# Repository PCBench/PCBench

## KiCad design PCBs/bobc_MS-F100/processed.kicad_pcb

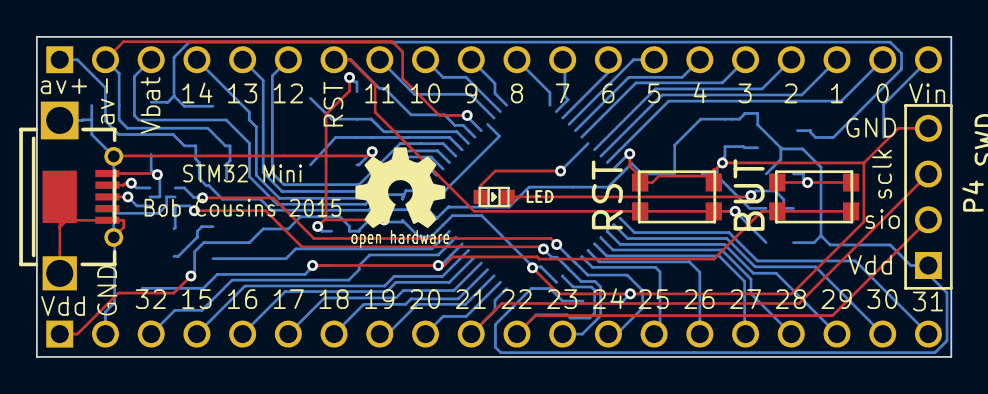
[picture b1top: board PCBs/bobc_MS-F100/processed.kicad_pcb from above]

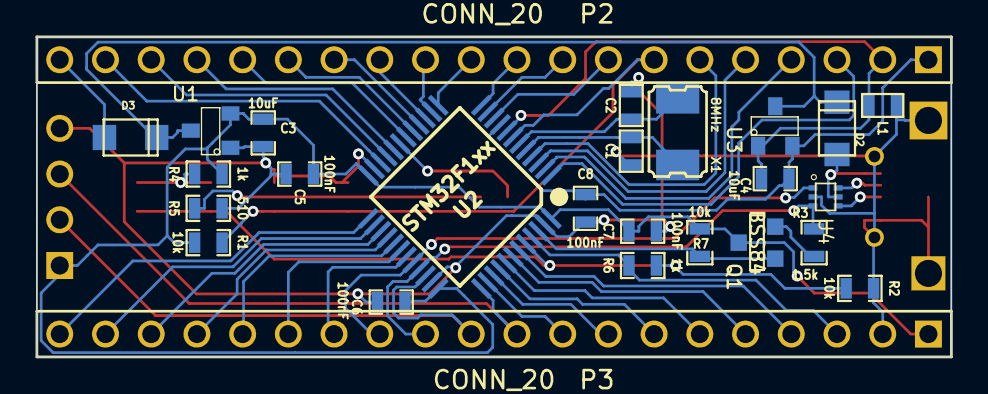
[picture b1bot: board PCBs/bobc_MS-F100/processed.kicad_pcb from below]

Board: 2 copper layers, 50.8 x 17.8 mm, 33 parts (26 on the bottom side), 52 nets.

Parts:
C1, C2: 20pF; SM0603_Capa
C3, C4: 10uF; SM0603_Capa
C5, C6, C7, C8: 100nF; SM0603_Capa
D1: LED; Led_0603
D2, D3: DIOD; do219ab
L1: IND; SM0603
M1: LOGO_OSHW; Logo_silk_OSHW_6x6mm
M2: PCB_GREEN_RMC; PCB_GREEN
P1: USBCONN; USB_MICRO_RMC
P2, P3: CONN_20; pin_header_2.54mm_1x20
P4: SWD; pin_header_2.54mm_1x4
Q1: BSS84; SOT23GDS
R1, R2, R7: 10k; SM0603_Resistor
R3: 1.5k; SM0603_Resistor
R4, R6: 1k; SM0603_Resistor
R5: 510; SM0603_Resistor
SW1: RST; SW_C&K_KMR4
SW2: BUT; SW_C&K_KMR4
U1, U3: MCP1703_SOT23; SOT23
U2: STM32F1xx; QFP48_0.5mm_7x7mm_SOT313_LPC1343
U4: NUF2042; SOT-563
X1: 8MHz; crystal_smd_5x3.2mm

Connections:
/AV+: C4.1, C8.1, P2.1, U2.9, U3.2
/AV-: C4.2, L1.2, P2.2, U2.8, U3.1
/BOOT0: R2.1, R6.2, SW2.1, U2.44
/D0: P2.19, U2.22
/D1: P2.18, U2.21
/D2: P2.17, U2.20
/D3: P2.16, U2.18
/D4: P2.15, U2.17
/D5: P2.14, U2.16
/D6: P2.13, U2.15
/D7: P2.12, U2.14
/D8: P2.11, U2.13
/D9: P2.10, U2.12
/D10: P2.9, U2.11
/D11: P2.8, U2.10
/D12: P2.6, U2.4
/D13: P2.5, U2.3
/D14: P2.4, U2.2
/D15: P3.4, U2.43
/D16: P3.5, U2.42
/D17: P3.6, U2.41
/D18: P3.7, U2.40
/D19: P3.8, U2.39
/D20: P3.9, U2.38
/D21_SWCLK: P3.10, P4.3, U2.37
/D22_SWIO: P3.11, P4.2, U2.34
/D23_USBDP: P3.12, R3.2, U2.33, U4.3
/D24_USBDM: P3.13, U2.32, U4.1
/D25: P3.14, U2.31
/D26: P3.15, U2.30
/D27: P3.16, U2.29
/D28: P3.17, U2.28
/D29: P3.18, U2.27
/D30: P3.19, U2.26
/D31: P3.20, U2.25
/D32: P3.3, R6.1, U2.45
/D33: D1.1, U2.19
/DISC: Q1.G, R7.2, U2.46
/VBAT: P2.3, U2.1
/VBUS: D2.1, P1.1, U4.5
/nRESET: P2.7, R1.2, SW1.2, U2.7
GND: C1.2, C2.2, C3.2, C5.2, C6.2, C7.2, C8.2, L1.1, P1.4, P1.5, P3.2, P4.4, R2.2, R5.2, SW1.1, U1.1, U2.23, U2.35, U2.47, U4.2
unnamed: R4.2, SW2.2
unnamed: D1.2, R5.1
unnamed: Q1.S, R3.1
unnamed: C1.1, U2.5, X1.1
unnamed: C2.1, U2.6, X1.2
unnamed: P1.3, U4.4
unnamed: D2.2, D3.2, U1.3, U3.3
unnamed: P1.2, U4.6
VDD: C3.1, C5.1, C6.1, C7.1, P3.1, P4.1, Q1.D, R1.1, R4.1, R7.1, U1.2, U2.24, U2.36, U2.48
VIN: D3.1, P2.20

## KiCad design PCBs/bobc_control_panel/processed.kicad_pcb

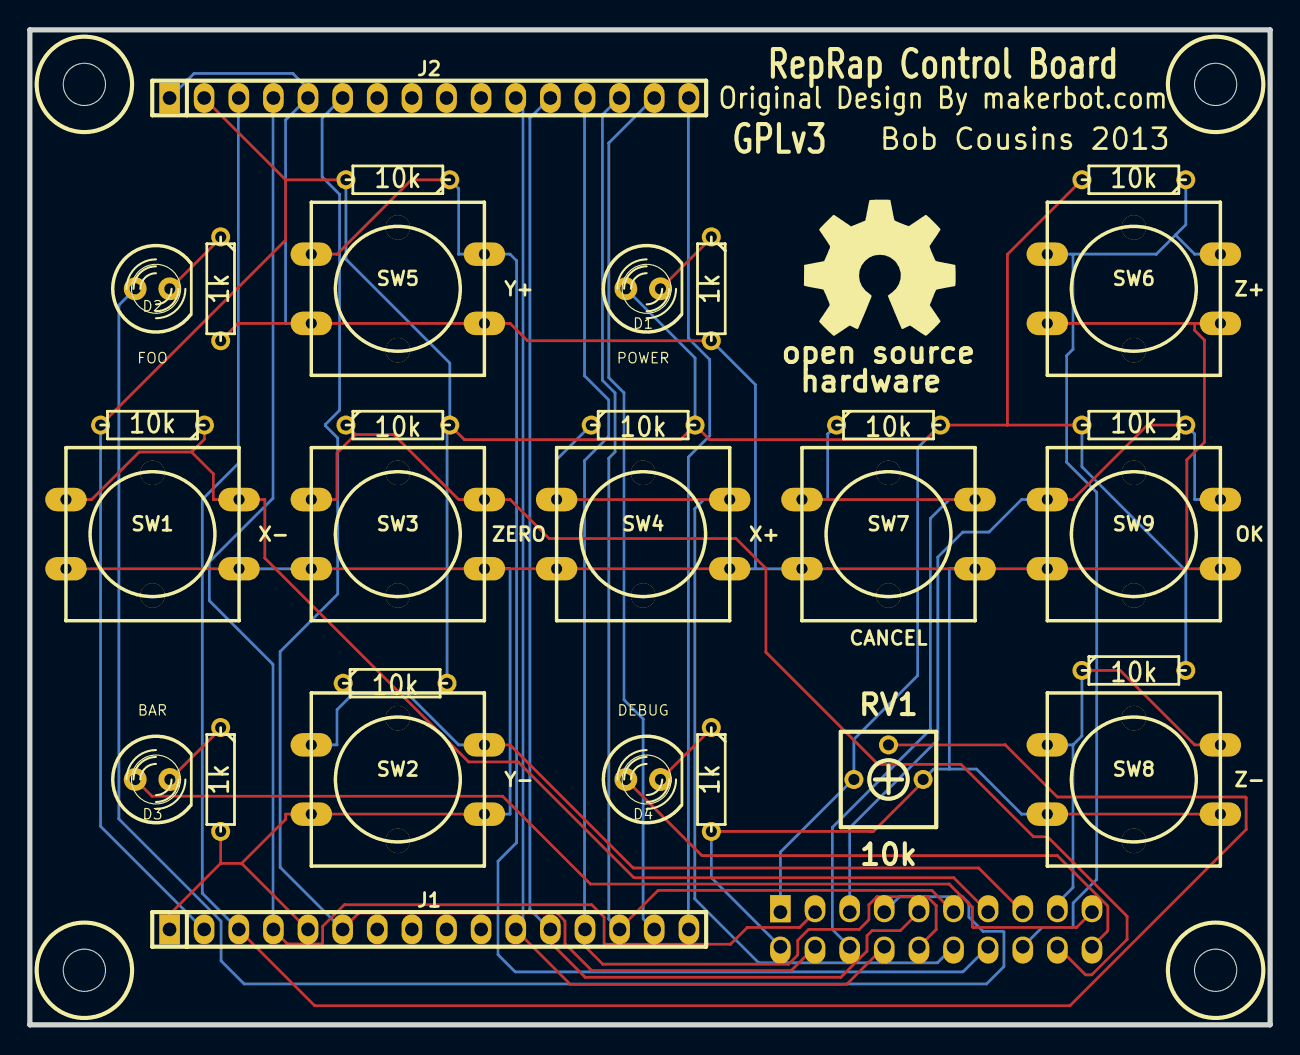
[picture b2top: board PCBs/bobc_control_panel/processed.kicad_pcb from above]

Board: 2 copper layers, 91.0 x 73.0 mm, 35 parts (1 on the bottom side), 27 nets.

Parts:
D1: POWER; LED-5MM
D2: FOO; LED-5MM
D3: BAR; LED-5MM
D4: DEBUG; LED-5MM
G1: LOGO; OSHW_logo_2
HOLE_M31, HOLE_M32, HOLE_M33, HOLE_M34: P***; HOLE_M3
J1, J2: LCD; pin_strip_16
P1: CONN_10X2; vasch_strip_10x2
R1, R2, R3, R4, R5, R7, R9, R11, R13: 10k; R3
R6, R8, R10, R12: 1k; R3
RV1: 10k; TRIM-BOURNS-3362
SW1: X-; SW_PUSH-12mm_RMC
SW2: Y-; SW_PUSH-12mm_RMC
SW3: ZERO; SW_PUSH-12mm_RMC
SW4: X+; SW_PUSH-12mm_RMC
SW5: Y+; SW_PUSH-12mm_RMC
SW6: Z+; SW_PUSH-12mm_RMC
SW7: CANCEL; SW_PUSH-12mm_RMC
SW8: Z-; SW_PUSH-12mm_RMC
SW9: OK; SW_PUSH-12mm_RMC

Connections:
/B_CANCEL: P1.6, R9.1, SW7.1
/B_OK: P1.5, R13.1, SW9.1
/B_X+: P1.12, R4.1, SW4.1
/B_X-: P1.13, R1.1, SW1.1
/B_Y+: P1.14, R5.1, SW5.1
/B_Y-: P1.15, R2.1, SW2.1
/B_Z+: P1.16, R7.1, SW6.1
/B_Z-: P1.17, R11.1, SW8.1
/B_ZERO: P1.18, R3.1, SW3.1
/LCD_BACKLIGHT+: J1.15, J2.15
/LCD_BACKLIGHT-: J1.16, J2.16
/LCD_CONTRAST: J1.3, J2.3, RV1.2
/LCD_D4: J1.11, J2.11, P1.8
/LCD_D5: J1.12, J2.12, P1.9
/LCD_D6: J1.13, J2.13, P1.10
/LCD_D7: J1.14, J2.14, P1.11
/LCD_ENABLE: J1.6, J2.6, P1.4
/LCD_RS: J1.4, J2.4, P1.3
/LED1: D2.1, P1.7
/LED2: D3.1, P1.19
/LED3: D4.1, P1.20
GND: J1.1, J1.5, J2.1, J2.5, P1.2, R6.2, R8.2, R10.2, R12.2, RV1.3, SW1.2, SW2.2, SW3.2, SW4.2, SW5.2, SW6.2, SW7.2, SW8.2, SW9.2
unnamed: D2.2, R8.1
unnamed: D1.2, R6.1
unnamed: D4.2, R12.1
unnamed: D3.2, R10.1
VCC: D1.1, J1.2, J2.2, P1.1, R1.2, R2.2, R3.2, R4.2, R5.2, R7.2, R9.2, R11.2, R13.2, RV1.1

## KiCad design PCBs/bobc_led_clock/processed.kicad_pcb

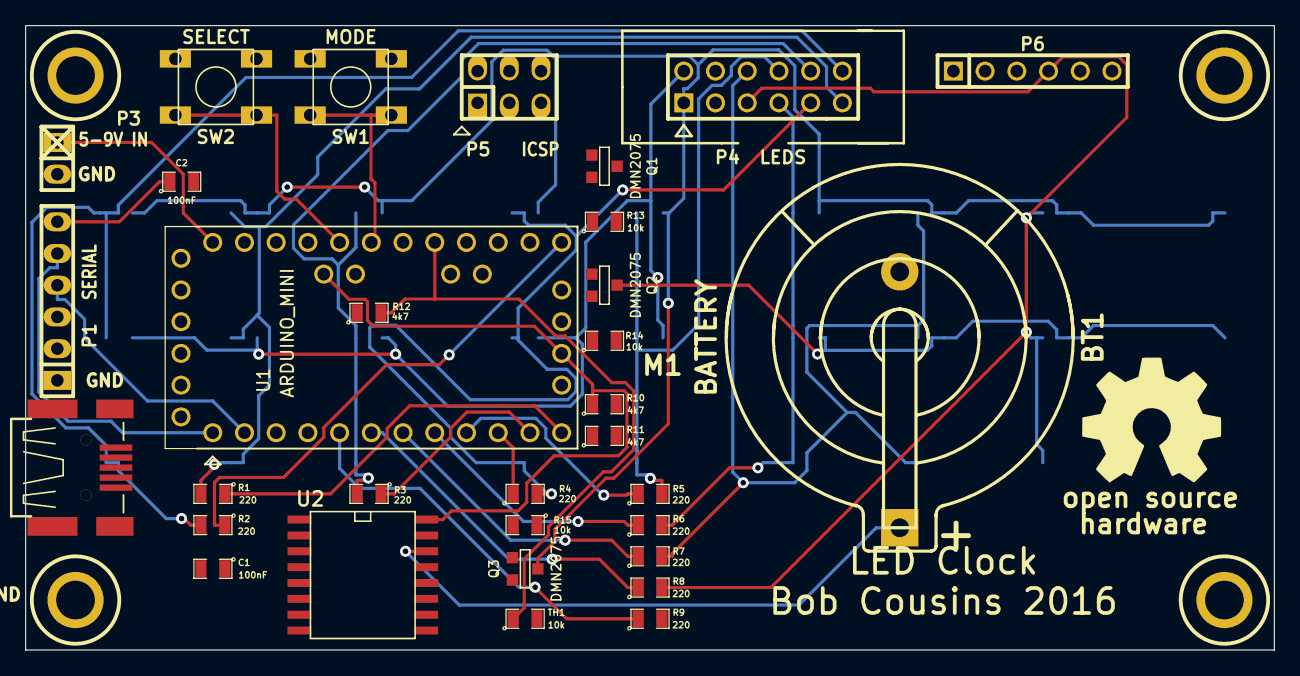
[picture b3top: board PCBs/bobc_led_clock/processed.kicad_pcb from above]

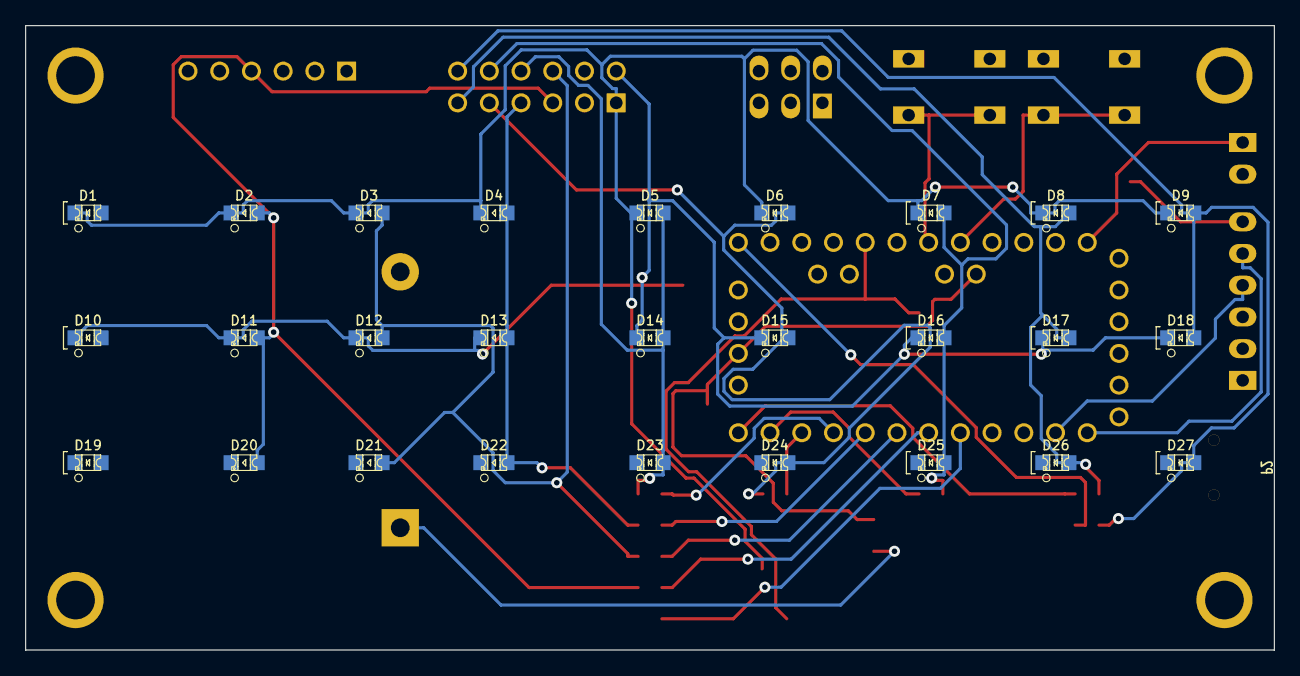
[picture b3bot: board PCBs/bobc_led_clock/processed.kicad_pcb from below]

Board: 2 copper layers, 100.0 x 50.0 mm, 65 parts (27 on the bottom side), 28 nets.

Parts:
BT1: BATTERY; keystone_106
C1, C2: 100nF; SM0805
D1, D7, D8, D9, D10, D16, D17, D18, D19, D25, D26, D27: LED; LED-0805_RED
D2, D3, D4, D11, D12, D13, D20, D21, D22: LED; LED-0805_GREEN
D5, D6, D14, D15, D23, D24: LED; LED-0805_BLUE
H1, H2, H3, H4: HOLE_RMC; HOLE_M3
M1: PCB_GREEN_RMC
M2: LOGO_OSHW; OSHW_logo_2
P1: SERIAL; pin_strip_6
P2: CONN_5; CONN_MiniAB_SMT_RMC
P3: 5-9V IN; pin_strip_2
P4: LEDS; PIN_ARRAY_6x2_RMC
P5: ICSP; pin_strip_3x2
P6: CONN_6; PIN_ARRAY-6X1
Q1, Q2, Q3: DMN2075; SOT23GDS
R1, R2, R3, R4, R5, R6, R7, R8, R9: 220; SM0805
R10, R11, R12: 4k7; SM0805
R13, R14, R15: 10k; SM0805
SW1: MODE; SW_6x6_MULTI
SW2: SELECT; SW_6x6_MULTI
TH1: 10k; SM0805
U1: ARDUINO_MINI
U2: DS3231N; SO16L

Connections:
/SCL: R10.1, U1.A5, U2.16
/SW1: SW1.1, U1.A2
/SW2: SW2.1, U1.A3
/VIN: P3.1, U1.VIN
COL2: D2.1, D11.1, D20.1, P4.5, P6.4, R8.2
COL3: D3.1, D12.1, D21.1, P4.6, R7.2
COL4: D4.1, D13.1, D22.1, P4.7, R6.2
COL5: D5.1, D14.1, D23.1, P4.8, R5.2
COL6: D6.1, D15.1, D24.1, P4.9, R4.2
COL7: D7.1, D16.1, D25.1, P4.10, R3.2
COL8: D8.1, D17.1, D26.1, P4.11, R2.2
COL9: D9.1, D18.1, D27.1, P4.12, R1.2
unnamed: R5.1, U1.6
unnamed: R6.1, U1.5
unnamed: R7.1, U1.4
unnamed: R8.1, U1.3
unnamed: R9.1, U1.2
unnamed: R4.1, U1.7
unnamed: C2.1, P1.6
unnamed: R1.1, U1.10
unnamed: R2.1, U1.9
unnamed: R3.1, U1.8
unnamed: R12.2, TH1.1, U1.A0
unnamed: BT1.1, U2.14
ROW1: D1.2, D2.2, D3.2, D4.2, D5.2, D6.2, D7.2, D8.2, D9.2, P4.1, Q3.D
ROW2: D10.2, D11.2, D12.2, D13.2, D14.2, D15.2, D16.2, D17.2, D18.2, P4.2, Q2.D
RX: P1.4, U1.0
TX: P1.5, U1.1

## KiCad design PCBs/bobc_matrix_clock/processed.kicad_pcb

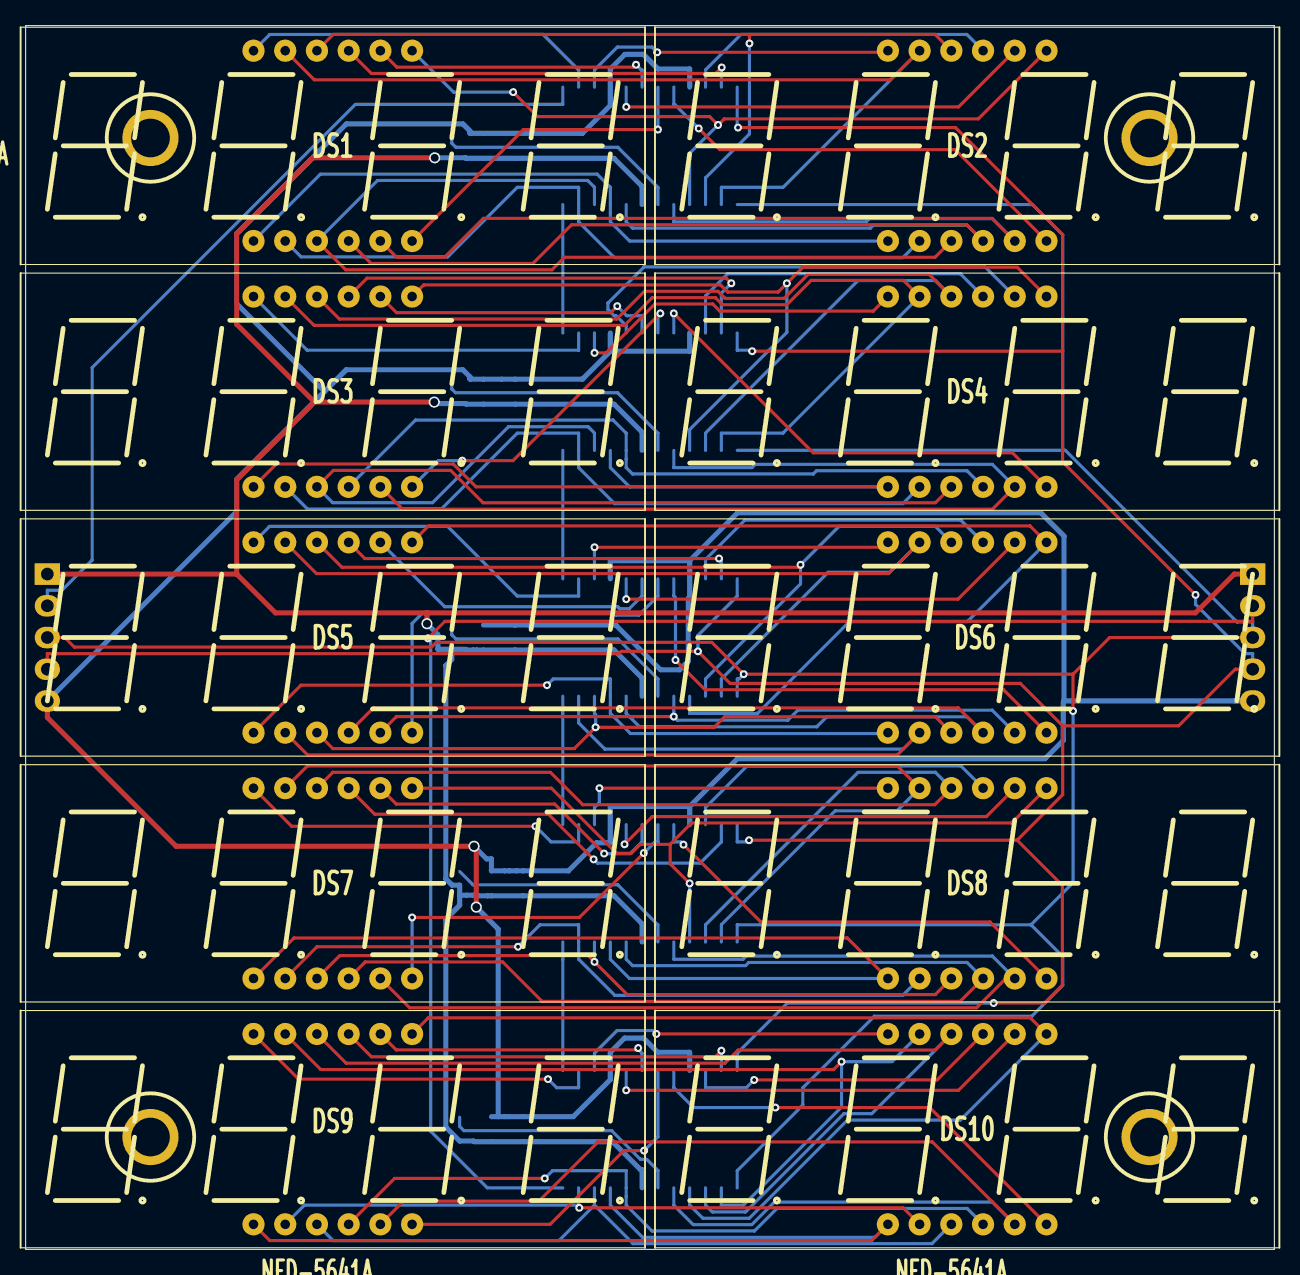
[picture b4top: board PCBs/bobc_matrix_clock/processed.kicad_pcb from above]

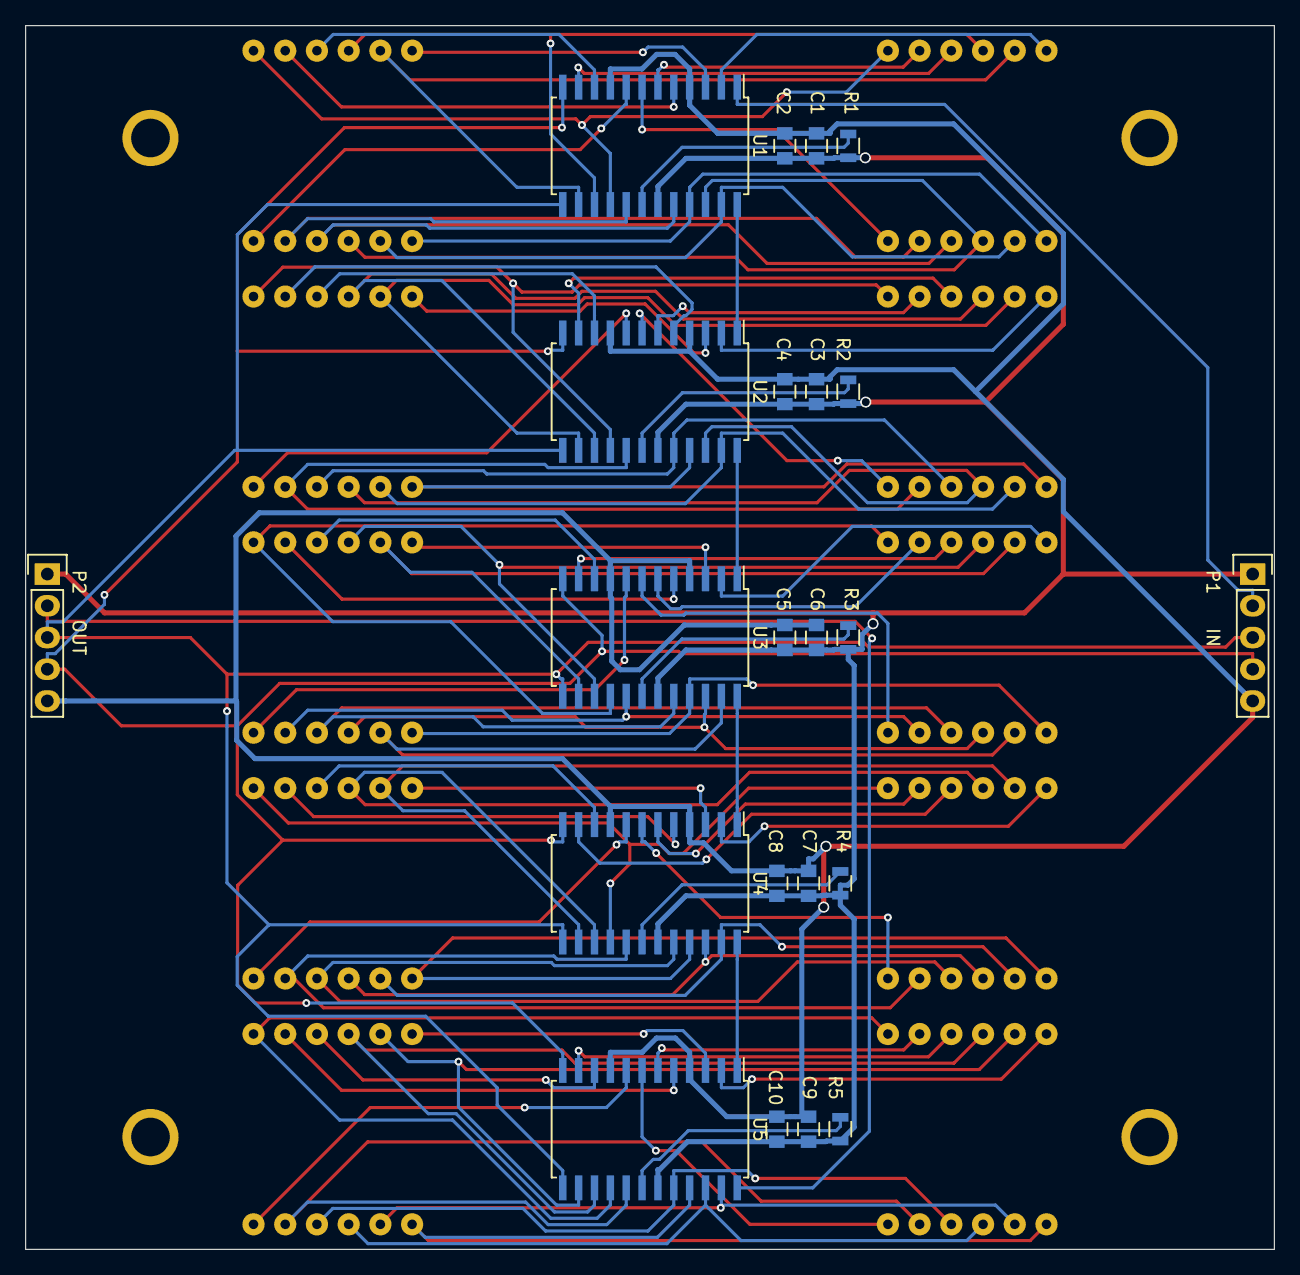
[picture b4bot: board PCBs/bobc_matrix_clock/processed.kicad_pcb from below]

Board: 2 copper layers, 100.0 x 98.0 mm, 36 parts (22 on the bottom side), 95 nets.

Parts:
C1, C3, C5, C7, C9: 10uF; C_0805
C2, C4, C6, C8, C10: 100nF; C_0805
DS1, DS2, DS3, DS4, DS5, DS6, DS7, DS8, DS9, DS10: NFD-5641A; NFD-5641
H1, H2, H3, H4: HOLE_RMC; HOLE_M3
P1: IN; Socket_Strip_Straight_1x05
P2: OUT; Socket_Strip_Straight_1x05
R1, R2, R3, R4, R5: 28k; R_0805
U1, U2, U3, U4, U5: MAX7219; SOIC-24_7.5x15.4mm_Pitch1.27mm

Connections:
/Digits Row 1/CLK: P1.3, P2.3, U1.13, U2.13, U3.13, U4.13, U5.13
/Digits Row 1/DIN: P1.2, U1.1
/Digits Row 1/LOAD: P1.4, P2.4, U1.12, U2.12, U3.12, U4.12, U5.12
/Digits Row 1/SEG_A: DS1.11, DS2.11, U1.14
/Digits Row 1/SEG_B: DS1.7, DS2.7, U1.16
/Digits Row 1/SEG_C: DS1.4, DS2.4, U1.20
/Digits Row 1/SEG_D: DS1.2, DS2.2, U1.23
/Digits Row 1/SEG_DP: DS1.3, DS2.3, U1.22
/Digits Row 1/SEG_E: DS1.1, DS2.1, U1.21
/Digits Row 1/SEG_F: DS1.10, DS2.10, U1.15
/Digits Row 1/SEG_G: DS1.5, DS2.5, U1.17
/Row 2/DIN: U1.24, U2.1
/Row 2/SEG_A: DS3.11, DS4.11, U2.14
/Row 2/SEG_B: DS3.7, DS4.7, U2.16
/Row 2/SEG_C: DS3.4, DS4.4, U2.20
/Row 2/SEG_D: DS3.2, DS4.2, U2.23
/Row 2/SEG_DP: DS3.3, DS4.3, U2.22
/Row 2/SEG_E: DS3.1, DS4.1, U2.21
/Row 2/SEG_F: DS3.10, DS4.10, U2.15
/Row 2/SEG_G: DS3.5, DS4.5, U2.17
/Row 3/DIN: U2.24, U3.1
/Row 3/SEG_A: DS5.11, DS6.11, U3.14
/Row 3/SEG_B: DS5.7, DS6.7, U3.16
/Row 3/SEG_C: DS5.4, DS6.4, U3.20
/Row 3/SEG_D: DS5.2, DS6.2, U3.23
/Row 3/SEG_DP: DS5.3, DS6.3, U3.22
/Row 3/SEG_E: DS5.1, DS6.1, U3.21
/Row 3/SEG_F: DS5.10, DS6.10, U3.15
/Row 3/SEG_G: DS5.5, DS6.5, U3.17
/Row 4/DIN: U3.24, U4.1
/Row 4/SEG_A: DS7.11, DS8.11, U4.14
/Row 4/SEG_B: DS7.7, DS8.7, U4.16
/Row 4/SEG_C: DS7.4, DS8.4, U4.20
/Row 4/SEG_D: DS7.2, DS8.2, U4.23
/Row 4/SEG_DP: DS7.3, DS8.3, U4.22
/Row 4/SEG_E: DS7.1, DS8.1, U4.21
/Row 4/SEG_F: DS7.10, DS8.10, U4.15
/Row 4/SEG_G: DS7.5, DS8.5, U4.17
/Row 5/DIN: U4.24, U5.1
/Row 5/DOUT: P2.2, U5.24
/Row 5/SEG_A: DS9.11, DS10.11, U5.14
/Row 5/SEG_B: DS9.7, DS10.7, U5.16
/Row 5/SEG_C: DS9.4, DS10.4, U5.20
/Row 5/SEG_D: DS9.2, DS10.2, U5.23
/Row 5/SEG_DP: DS9.3, DS10.3, U5.22
/Row 5/SEG_E: DS9.1, DS10.1, U5.21
/Row 5/SEG_F: DS9.10, DS10.10, U5.15
/Row 5/SEG_G: DS9.5, DS10.5, U5.17
GND: C1.2, C2.2, C3.2, C4.2, C5.2, C6.2, C7.2, C8.2, C9.2, C10.2, P1.5, P2.5, U1.4, U1.9, U2.4, U2.9, U3.4, U3.9, U4.4, U4.9, U5.4, U5.9
unnamed: DS1.6, U1.7
unnamed: DS1.8, U1.6
unnamed: DS1.9, U1.11
unnamed: DS1.12, U1.2
unnamed: DS2.6, U1.8
unnamed: DS2.8, U1.5
unnamed: DS2.9, U1.10
unnamed: DS2.12, U1.3
unnamed: DS3.6, U2.7
unnamed: DS3.8, U2.6
unnamed: DS3.9, U2.11
unnamed: DS3.12, U2.2
unnamed: DS4.6, U2.8
unnamed: DS4.8, U2.5
unnamed: DS4.9, U2.10
unnamed: DS4.12, U2.3
unnamed: DS5.6, U3.7
unnamed: DS5.8, U3.6
unnamed: DS5.9, U3.11
unnamed: DS5.12, U3.2
unnamed: DS6.6, U3.8
unnamed: DS6.8, U3.5
unnamed: DS6.9, U3.10
unnamed: DS6.12, U3.3
unnamed: DS7.6, U4.7
unnamed: DS7.8, U4.6
unnamed: DS7.9, U4.11
unnamed: DS7.12, U4.2
unnamed: DS8.6, U4.8
unnamed: DS8.8, U4.5
unnamed: DS8.9, U4.10
unnamed: DS8.12, U4.3
unnamed: DS9.6, U5.7
unnamed: DS9.8, U5.6
unnamed: DS9.9, U5.11
unnamed: DS9.12, U5.2
unnamed: DS10.6, U5.8
unnamed: DS10.8, U5.5
unnamed: DS10.9, U5.10
unnamed: DS10.12, U5.3
unnamed: R1.2, U1.18
unnamed: R2.2, U2.18
unnamed: R3.2, U3.18
unnamed: R4.2, U4.18
unnamed: R5.2, U5.18
VCC: C1.1, C2.1, C3.1, C4.1, C5.1, C6.1, C7.1, C8.1, C9.1, C10.1, P1.1, P2.1, R1.1, R2.1, R3.1, R4.1, R5.1, U1.19, U2.19, U3.19, U4.19, U5.19

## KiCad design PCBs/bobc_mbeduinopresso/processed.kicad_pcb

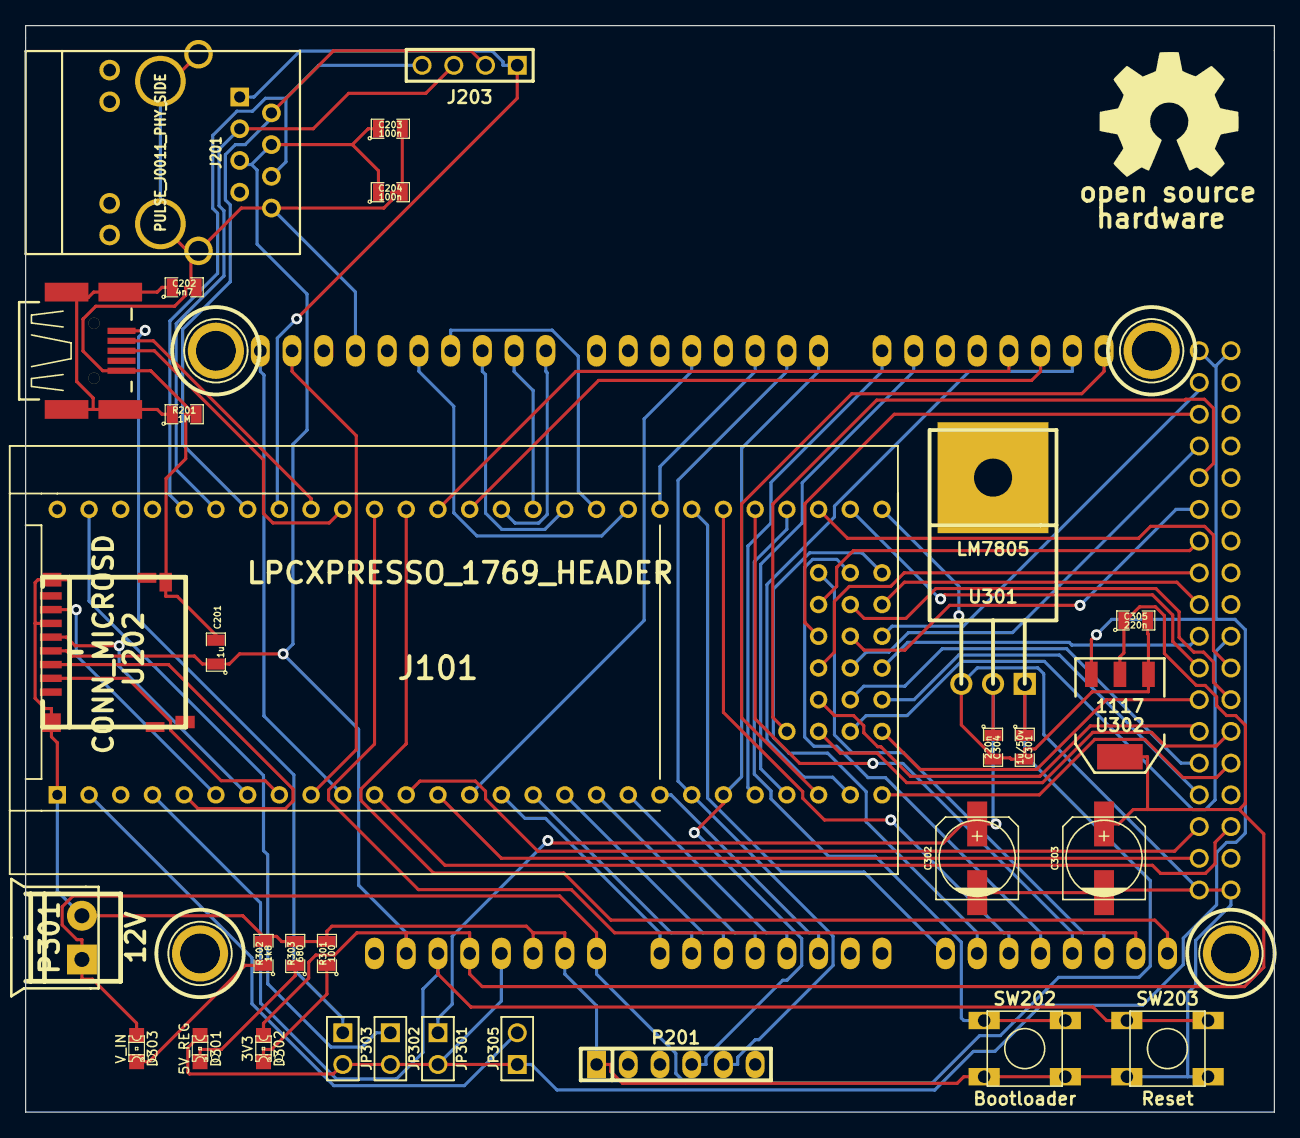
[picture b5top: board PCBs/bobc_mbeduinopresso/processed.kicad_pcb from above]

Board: 2 copper layers, 100.0 x 87.0 mm, 37 parts (0 on the bottom side), 77 nets.

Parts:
C201: 1u; SM0805
C202: 4n7; SM0805
C203, C204: 100n; SM0805
C301: 1u/50v; SM0805
C302, C303: 100u; c_elec_6.3x5.7
C304, C305: 220n; SM0805
D301: 5V_REG; LED-0805_GREEN
D302: 3V3; LED-0805_GREEN
D303: V_IN; LED-0805_GREEN
H201, H202, H203, H204: HOLE_RMC; HOLE_M3
J101: LPCXPRESSO_1769_HEADER; MBED_LPCXPRESSO
J201: PULSE_J0011_PHY_SIDE; RJ45_Halo_HFJ11
J203: Enet; PIN_ARRAY_4x1
JP301, JP302, JP303, JP305: JUMPER; PIN_ARRAY_2X1
M201: LOGO_OSHW; OSHW_logo_2
P201: SERIAL; pin_strip_6
P301: 12V; RMC-pt_1,5-2-3,5-h
R201: 1M; SM0805
R301: 100; SM0805
R302: 1k8; SM0805
R303: 680; SM0805
SHIELD101: ARDUINO_DUE_SHIELD; ARDUINO_MEGA_DUE_SHIELD_FOOTPRINT_RMC
SW202: Bootloader; SW_6x6_MULTI
SW203: Reset; SW_6x6_MULTI
U201: USBCONN; CONN_MiniAB_SMT_RMC
U202: CONN_MICROSD; MICRO_SD_DM3D
U301: LM7805; TO220
U302: 1117; SOT223

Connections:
*Bootloader: J101.51, SW202.1
*ETH_RD+: J101.33, J201.3, J203.3
*ETH_RD-: J101.32, J201.6, J203.4
*ETH_TD+: J101.35, J201.1, J203.1
*ETH_TD-: J101.34, J201.2, J203.2
*RESET: J101.4, SHIELD101.RST, SW203.1
*RX: J101.22, P201.4, SHIELD101.0
*TX: J101.21, P201.5, SHIELD101.1
*USB-D+: J101.37, U201.3
*USB-D-: J101.36, U201.2
+3.3V: C201.1, C203.1, C204.1, C303.1, C305.1, D302.1, J201.4, J201.5, SHIELD101.3V3, SHIELD101.IORF, U202.4, U302.2, U302.4
+5V: D301.1, JP301.2, JP302.2, JP303.2, JP305.1, SHIELD101.5V, SHIELD101.5V_4, SHIELD101.5V_5, U302.3
/Power/5V_REG: C302.1, C304.1, JP301.1, U301.3
AD4: J101.19, SHIELD101.AD4
AD5: J101.20, SHIELD101.AD5
CS_1: J101.8, U202.2
E0-DIR: J101.119, SHIELD101.28
E0-EN: J101.116, SHIELD101.42
E0-STEP: J101.104, SHIELD101.36
E1-DIR: J101.52, SHIELD101.41
E1-EN: J101.117, SHIELD101.39
E1-STEP: J101.105, SHIELD101.43
E2-DIR: J101.27, SHIELD101.47
E2-EN: J101.118, SHIELD101.45
E2-STEP: J101.106, SHIELD101.32
ESTOP: J101.53, SHIELD101.40
GND: C201.2, C202.2, C203.2, C204.2, C301.2, C302.2, C303.2, C304.2, C305.2, J101.1, J101.54, J201.8, J201.13, P201.1, P301.2, R201.2, R301.2, R302.2, R303.2, SHIELD101.GND, SW202.2, SW203.2, U201.4, U202.6, U202.9, U202.11, U301.2, U302.1
LPC_VIN: J101.2, JP305.2
MISO_0: J101.12, SHIELD101.50
MISO_1: J101.6, U202.7
MOSI_0: J101.11, SHIELD101.51
MOSI_1: J101.5, U202.3
unnamed: C202.1, R201.1, U201.5
unnamed: D301.2, R303.1
unnamed: D302.2, R301.1
unnamed: D303.2, R302.1
P0.4: J101.38, SHIELD101.AD14
P0.5: J101.39, SHIELD101.AD15
P0.21: J101.23, SHIELD101.14
P0.22: J101.24, SHIELD101.15
POWER1: J101.42, SHIELD101.8
POWER2: J101.43, SHIELD101.9
POWER3: J101.44, SHIELD101.10
POWER4: J101.45, SHIELD101.11
POWER5: J101.46, SHIELD101.12
POWER6: J101.47, SHIELD101.2
RXD2_SCL2: J101.41, SHIELD101.19
RXD3_SCL1: J101.10, SHIELD101.SCL1
SCK_0: J101.13, SHIELD101.52
SCK_1: J101.7, U202.5
SCL0: J101.26, SHIELD101.20
SDA0: J101.25, SHIELD101.21
SSEL_0: J101.14, SHIELD101.4
THERM0: J101.15, SHIELD101.AD0
THERM1: J101.16, SHIELD101.AD1
THERM2: J101.17, SHIELD101.AD2
THERM3: J101.18, SHIELD101.AD3
TXD2_SDA2: J101.40, SHIELD101.18
TXD3_SDA1: J101.9, SHIELD101.SDA1
VIN: C301.1, D303.1, P301.1, SHIELD101.V_IN, U301.1
VUSB1: J101.29, JP302.1
VUSB2: JP303.1, U201.1
X-DIR: J101.48, SHIELD101.AD8
X-EN: J101.113, SHIELD101.48
X-STEP: J101.101, SHIELD101.AD9
XMAX: J101.108, SHIELD101.30
XMIN: J101.107, SHIELD101.22
Y-DIR: J101.49, SHIELD101.AD10
Y-EN: J101.114, SHIELD101.46
Y-STEP: J101.102, SHIELD101.AD11
YMAX: J101.110, SHIELD101.38
YMIN: J101.109, SHIELD101.24
Z-DIR: J101.50, SHIELD101.AD12
Z-EN: J101.115, SHIELD101.44
Z-STEP: J101.103, SHIELD101.AD13
ZMAX: J101.112, SHIELD101.34
ZMIN: J101.111, SHIELD101.26

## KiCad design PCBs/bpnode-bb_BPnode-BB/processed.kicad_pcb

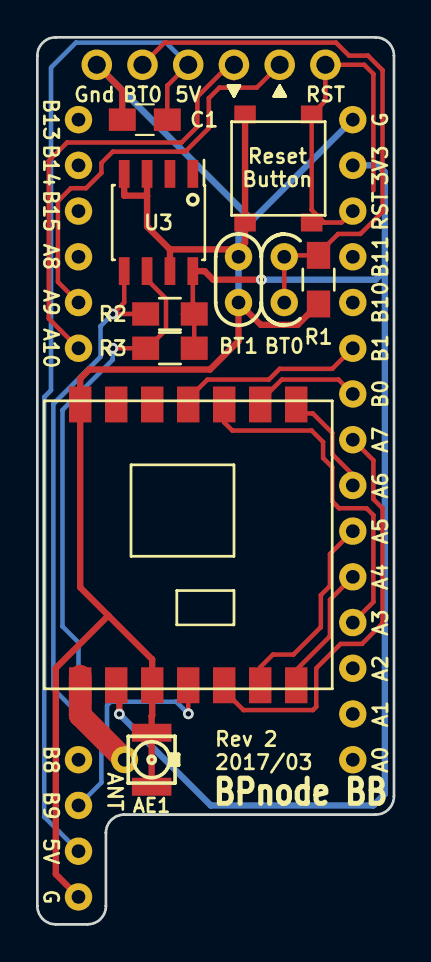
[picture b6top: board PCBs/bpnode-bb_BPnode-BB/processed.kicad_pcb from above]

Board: 2 copper layers, 19.8 x 49.3 mm, 10 parts (0 on the bottom side), 18 nets.

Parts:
AE1: Antenna_Shield; U.FL-COAX
C1: 0.1u; C_0805_HandSoldering
P1: CONN_01X06; Pin_Header_Angled_1x06_Pitch2.54mm
R1, R2, R3: R; R_0805_HandSoldering
SW1: SW_Push; SMD_BUTTON
U1: BP; BLUEPILL-EXTENSION
U2: RFM69; RFM69CW
U3: M24M02-DR; SOIC-8_3.9x4.9mm_Pitch1.27mm

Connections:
+3V3: R2.2, R3.2, U1.3V3, U2.2, U3.8
DIO0: U1.PB0, U2.9
DIO1: U1.PB1, U2.11
DIO2: U1.PA3, U2.10
DIO3: U1.PB9, U2.4
DTR: P1.6, SW1.1, U1.NRST
GND: AE1.2, C1.2, P1.1, R1.1, SW1.2, U1.G, U1.PB2, U2.3, U2.14, U3.3, U3.4, U3.7
MISO: U1.PA6, U2.8
MOSI: U1.PA7, U2.5
unnamed: AE1.1, U2.1
RTS: P1.2, R1.2, U1.BOOT
RX: P1.5, U1.PA9
SCL: R3.1, U1.PB6, U3.6
SCLK: U1.PA5, U2.6
SDA: R2.1, U1.PB7, U3.5
SSEL: U1.PA4, U2.7
TX: P1.4, U1.PA10
Vin: C1.1, P1.3, U1.5V

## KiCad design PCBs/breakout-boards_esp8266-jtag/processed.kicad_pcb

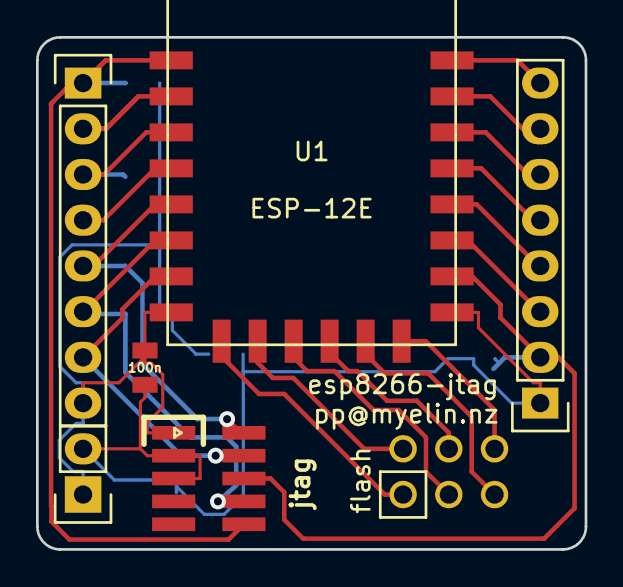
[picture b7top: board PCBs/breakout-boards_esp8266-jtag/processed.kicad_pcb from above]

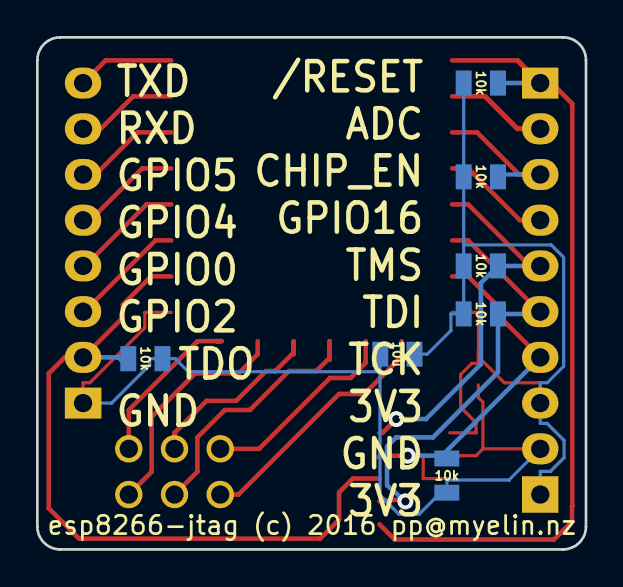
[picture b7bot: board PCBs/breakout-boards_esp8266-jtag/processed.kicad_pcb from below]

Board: 2 copper layers, 30.5 x 28.4 mm, 14 parts (7 on the bottom side), 22 nets.

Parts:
C1: 10u; C0805_nosilkscreen
C2: 100n; C0805_nosilkscreen
CON1: jtag; pin_array_5x2_50mil_smd
P1, P3: CONN_01X08; Pin_Header_Straight_1x08
P2: flash; pin_array_2x3_100mil_pth
P4: CONN_01X02; Pin_Header_Straight_1x02
R1, R2, R3, R4, R5, R6: 10k; R0805_nosilkscreen
U1: ESP-12E; ESP8266-ESP-12E

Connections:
/3v3: C1.1, C2.1, CON1.1, P1.8, P4.1, R1.2, R2.2, R4.1, R5.1, U1.8
/adc: P1.2, U1.2
/chip_en: P1.3, R2.1, U1.3
/cs0: P2.1, U1.9
/gnd: C1.2, C2.2, CON1.3, CON1.5, P3.1, P4.2, R3.1, R6.1, U1.15
/gpio0: P3.4, U1.18
/gpio2: P3.3, U1.17
/gpio4: P3.5, U1.19
/gpio5: P3.6, U1.20
/gpio9: P2.3, U1.11
/gpio10: P2.4, U1.12
/gpio16: P1.4, U1.4
/miso: P2.2, U1.10
/mosi: P2.5, U1.13
/nreset: CON1.10, P1.1, R1.1, U1.1
/sclk: P2.6, U1.14
/tck: CON1.4, P1.7, R6.2, U1.7
/tdi: CON1.8, P1.6, R5.2, U1.6
/tdo: CON1.6, P3.2, R3.2, U1.16
/tms: CON1.2, P1.5, R4.2, U1.5
/u0rxd: P3.7, U1.21
/u0txd: P3.8, U1.22

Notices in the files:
PCBs/bobc_MS-F100/processed.kicad_pcb:
Copyright Under the Creative Commons Attribution License
PCBs/bobc_control_panel/processed.kicad_pcb:
GPLv3
PCBs/breakout-boards_esp8266-jtag/processed.kicad_pcb:
esp8266-jtag (c) 2016 pp@myelin.nz
